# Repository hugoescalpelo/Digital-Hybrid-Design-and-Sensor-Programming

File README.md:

# Digital Hybrid Design and Sensor Programming
 Circuits, sensors programming and 3D printed Parts

**Digital Hybrid**

*Digital Hybrid* is a project from [Anni Garza Lau](http://www.annigarzalau.com/ "Anni Garza Lau") as part of [ACT](http://https://www.artecienciaytecnologias.mx/ "ACT") (Art, Cience and Technology Grant from Secretaria de Cultura, Mexico). This project is a collaboration between Anni Garza Lau, [Vladimir Sánchez Garrido](https://www.linkedin.com/in/vladimirsaga/ "Vladimir Sanches Garrido"), [Eddie Castañeda](https://2-2-0.online/ "Eddie Castañeda"), [Mariel Paredes](https://www.instagram.com/marielfashionfit/ "Mariel Paredes") y [Hugo Escalpelo](http://hugoescalpelo.com "Hugo Escalpelo").

*Digital Hybrid* is an art and technology project composed of a suit full of sensors and an artificial intelligence with its own personality. The sensors report the vital signs of their user and information about the environment in which they are. This information influences the behavior and vital signs of artificial intelligence, which is programmed to survive and feel pleasure and pain. Under Reinforcement Learning rules, artificial intelligence interacts with social networks and the contextual information at its disposal, sending sound messages, text and stimuli to the user to transform their behavior in their favor, however, it is expected that this behavior will become a win-win interaction.

**Role division**

Below is the division of roles.

- Anni Garza Lau. Creativa, user of the Digital Hybrid suit, Project Director.
- Mariel Paredes. Fashion designer.
- Eddie Castañeda. Computer vision manager
- Yunuen SaGa. Artificial intelligence developer, contextualizer developer and data visualization
- Hugo Escalpelo. Circuit designer, designer of 3D printed parts.

**Software Needed**

*3D printed Parts*

- SolidWorks 2020

*Laser Cut Parts*

- InkScape

*Circuits*

- Autidesk Eagle

*nVidia Jetson*

- L4T 4.3
- Ubuntu 18.04 LTS
- LibRealsense-utils
- LibRealsense-dev
- JetPack Installer 3.2.1
- NodeJS 14 LTS
- NodeRed 1.2.7
- NPM
- node-red-node-serialport Nodes
- node-red-node-twitter Nodes
- node-red-dashboard Nodes
- node-red-contrib-fitbit Nodes

**General System Description**

This diagram shows working stages at electronic level. This diagram does not includes IA systems.

**How to do it**

Video tutorials soon to be added.

**Instructions**

This is a big and complex Project. See Instructions Folder for more details on the many stages of reproducing this project.

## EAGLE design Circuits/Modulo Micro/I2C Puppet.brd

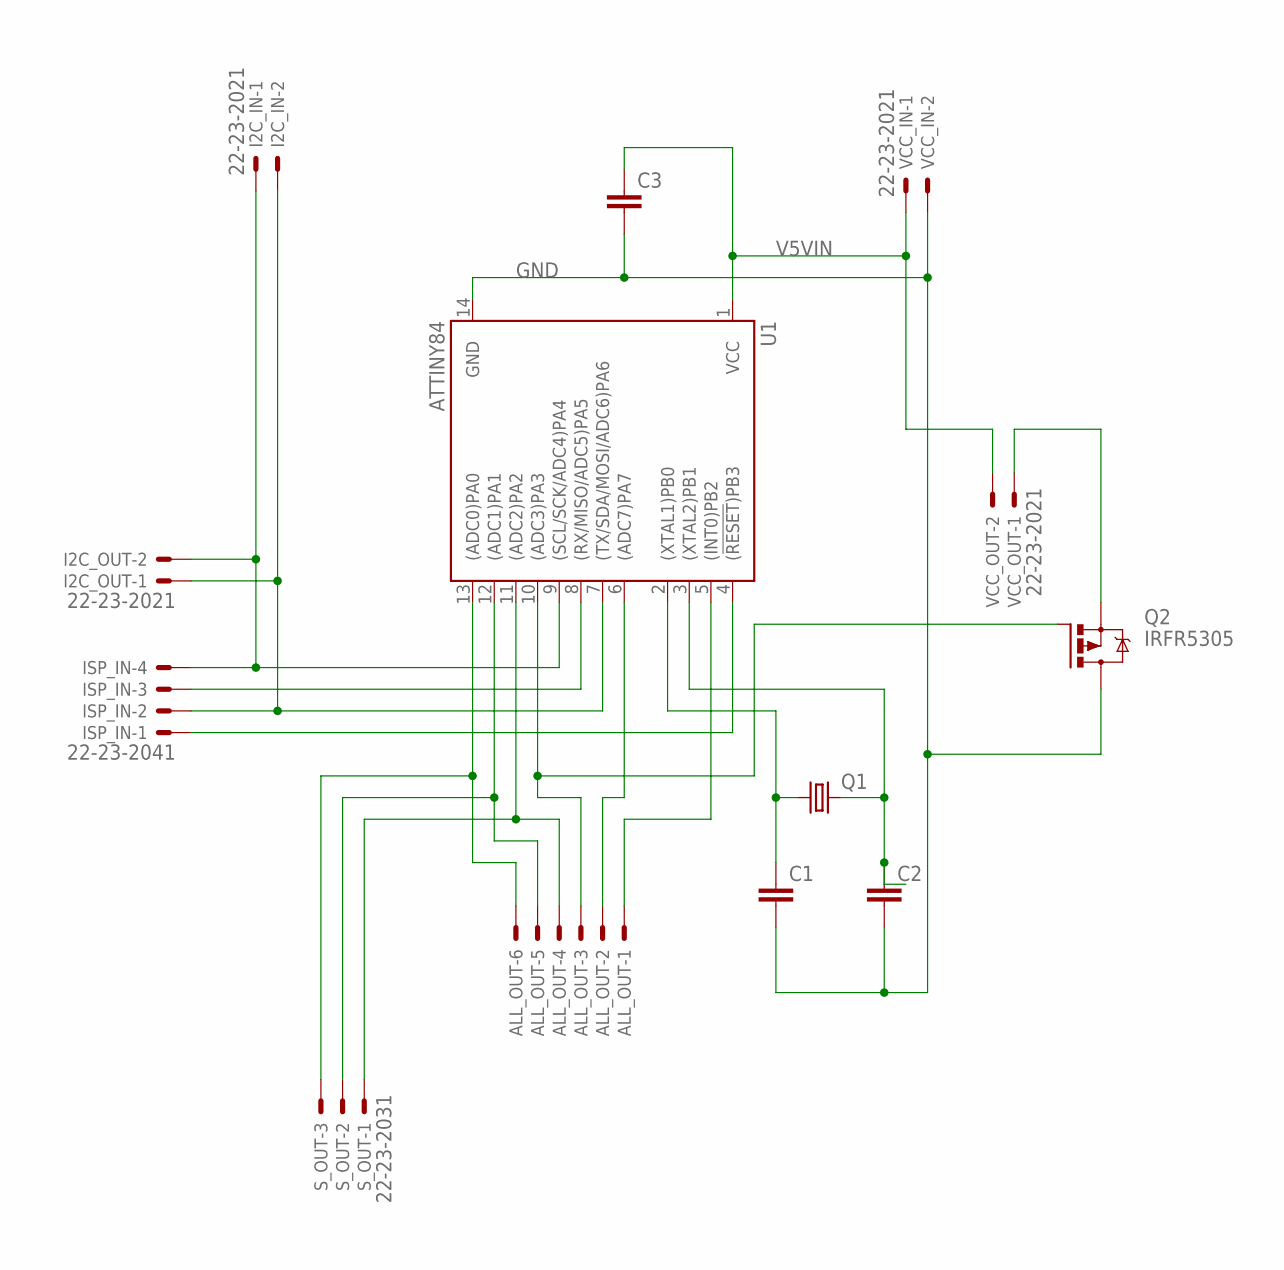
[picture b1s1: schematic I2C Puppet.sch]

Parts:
ALL_OUT: 22-23-2061
C1, C2, C3: C-EUC1210; C1210
I2C_IN, I2C_OUT: 22-23-2021
ISP_IN: 22-23-2041
Q1: CRYSTALHC49UP; HC49UP
Q2: IRFR5305; D-PAK_TO252AA
S_OUT: 22-23-2031
U1: ATTINY84; SO14
VCC_IN: 22-23-2021
VCC_OUT: 22-23-2021

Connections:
GND: C1.2, C2.2, C3.2, Q2.4 (D), U1.14 (GND), VCC_IN.2
unnamed: ALL_OUT.4, S_OUT.1, U1.11 ((ADC2)PA2)
unnamed: I2C_IN.1, I2C_OUT.2, ISP_IN.4, U1.9 ((SCL/SCK/ADC4)PA4)
unnamed: I2C_IN.2, I2C_OUT.1, ISP_IN.2, U1.7 ((TX/SDA/MOSI/ADC6)PA6)
unnamed: C1.1, Q1.1, U1.2 ((XTAL1)PB0)
unnamed: C2.1, Q1.2, U1.3 ((XTAL2)PB1)
unnamed: ISP_IN.1, U1.4 ((!RESET!)PB3)
unnamed: Q2.3 (S), VCC_OUT.1
unnamed: ISP_IN.3, U1.8 ((RX/MISO/ADC5)PA5)
unnamed: ALL_OUT.6, S_OUT.3, U1.13 ((ADC0)PA0)
unnamed: ALL_OUT.5, S_OUT.2, U1.12 ((ADC1)PA1)
unnamed: ALL_OUT.3, Q2.1 (G), U1.10 ((ADC3)PA3)
unnamed: ALL_OUT.2, U1.6 ((ADC7)PA7)
unnamed: ALL_OUT.1, U1.5 ((INT0)PB2)
V5VIN: C3.1, U1.1 (VCC), VCC_IN.1, VCC_OUT.2

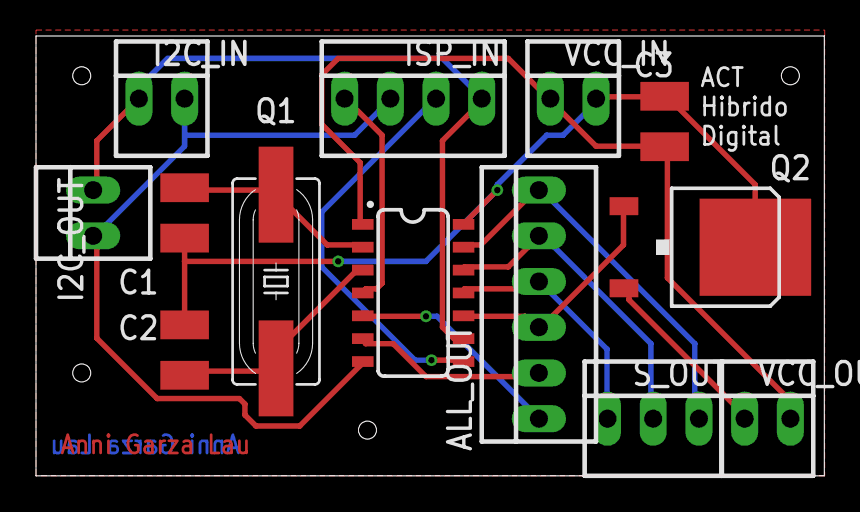
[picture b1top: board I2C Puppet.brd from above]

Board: 2 copper layers, 43.8 x 24.4 mm, 13 parts (0 on the bottom side), 15 nets.

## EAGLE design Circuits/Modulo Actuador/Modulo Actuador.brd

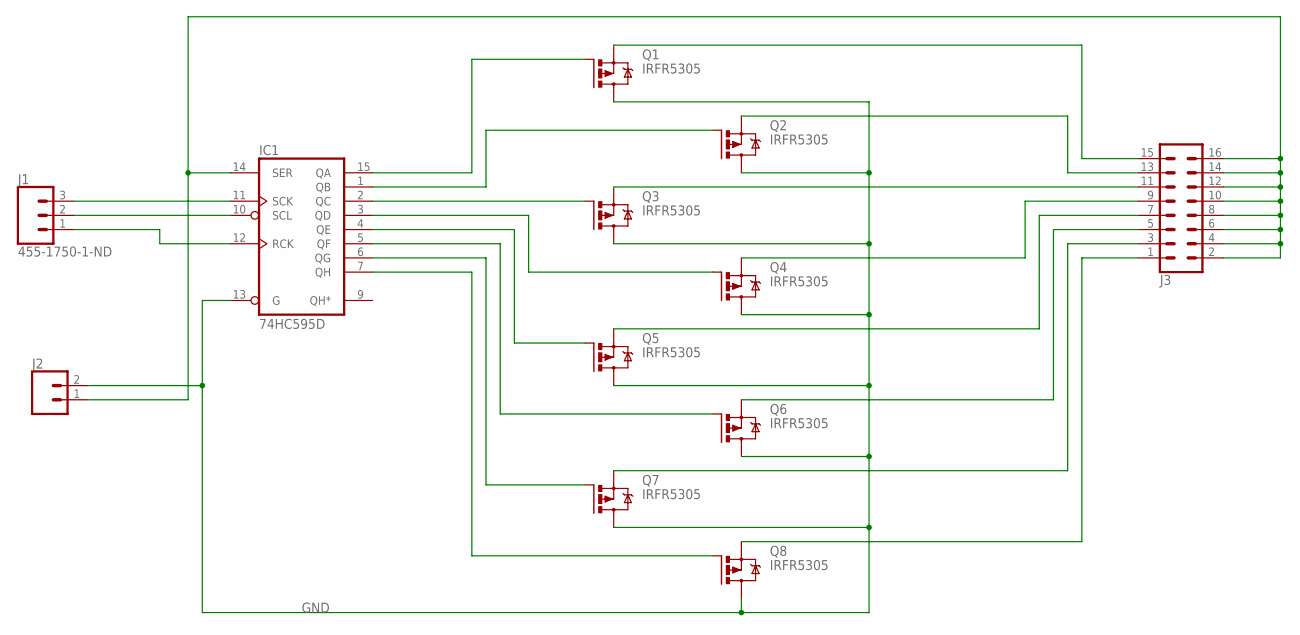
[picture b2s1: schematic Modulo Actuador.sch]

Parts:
IC1: 74HC595D; SO16
J1: 455-1750-1-ND; 1X03
J2: CONN_02; 1X02
J3: CONN_08X2_HEADER; 2X8
Q1, Q2, Q3, Q4, Q5, Q6, Q7, Q8: IRFR5305; D-PAK_TO252AA

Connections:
GND: IC1.8 (GND), IC1.13 (G), J2.2, Q1.4 (D), Q2.4 (D), Q3.4 (D), Q4.4 (D), Q5.4 (D), Q6.4 (D), Q7.4 (D), Q8.4 (D)
unnamed: IC1.14 (SER), J2.1, J3.2, J3.4, J3.6, J3.8, J3.10, J3.12, J3.14, J3.16
unnamed: IC1.12 (RCK), J1.1
unnamed: IC1.10 (SCL), J1.2
unnamed: IC1.11 (SCK), J1.3
unnamed: IC1.15 (QA), Q1.1 (G)
unnamed: IC1.1 (QB), Q2.1 (G)
unnamed: IC1.2 (QC), Q3.1 (G)
unnamed: IC1.3 (QD), Q4.1 (G)
unnamed: IC1.4 (QE), Q5.1 (G)
unnamed: IC1.5 (QF), Q6.1 (G)
unnamed: IC1.6 (QG), Q7.1 (G)
unnamed: IC1.7 (QH), Q8.1 (G)
unnamed: J3.15, Q1.3 (S)
unnamed: J3.13, Q2.3 (S)
unnamed: J3.11, Q3.3 (S)
unnamed: J3.1, Q8.3 (S)
unnamed: J3.3, Q7.3 (S)
unnamed: J3.5, Q6.3 (S)
unnamed: J3.7, Q5.3 (S)
unnamed: J3.9, Q4.3 (S)
VCC: IC1.16 (VCC)

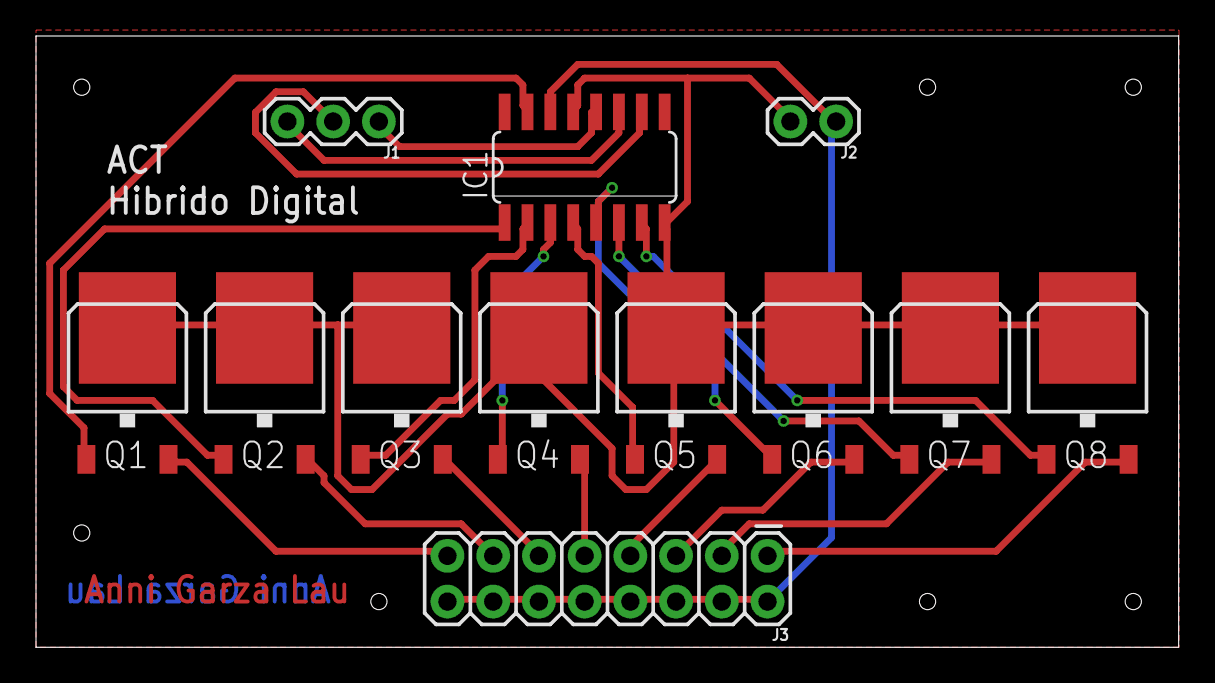
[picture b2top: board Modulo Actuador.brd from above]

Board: 2 copper layers, 63.5 x 34.0 mm, 12 parts (0 on the bottom side), 21 nets.

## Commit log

2021-03-20 Update ReadMe.md
    Project introduction
2021-03-20 Solidos agregados
    Se agregaron todos los solidos
2021-03-20 Note due to large size model
    Large size model note added, nVidia Jetson model too big. Software needed list added to readme.md
2021-03-20 Circuits Added
    Circuits Added
2021-03-20 Laser cut Parts Added
    Laser cut Parts Added
2021-03-20 Eagle Libraries Added
    Eagle Libraries Added
2021-03-20 Microntroller programms added
    Microntroller programms added
2021-03-20 Descriptions added
    DataBase, and protocols descriptions added
2021-03-20 Diagram Added
    Funcional diagram added to ReadMe.md
2021-03-20 NodeRed Flows added
    NodeRed Flows added
2021-03-20 Note added
    To ReadMe.md
2021-03-20 Part List Added
    Part List Added
2021-03-20 Instructions scheme added
    Instructions scheme added
2021-03-20 Instructions notes added
    To ReadMe.md
2021-03-20 Errata
    Errata

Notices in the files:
parts and their libraries:
SparkFun-Connectors: Licensing: Creative Commons ShareAlike 4.0 International - https://creativecommons.org/licenses/by-sa/4.0
